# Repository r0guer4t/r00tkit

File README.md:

This handheld is meant to lower the barrier to hardware hacking.
Simple in its design and purpose. 
Superb at one thing because it neednt be bad at all things.

Technical specifications;
	Rockchip RK3328@1.5GHZ
	4 GB LPDDR3 
	32 GB microSD card
	ESP32s2
	5 in. LCD over HDMI
	2 USB 2.0 ports
	1 USB 3.0 port
	1 Ethernet jack

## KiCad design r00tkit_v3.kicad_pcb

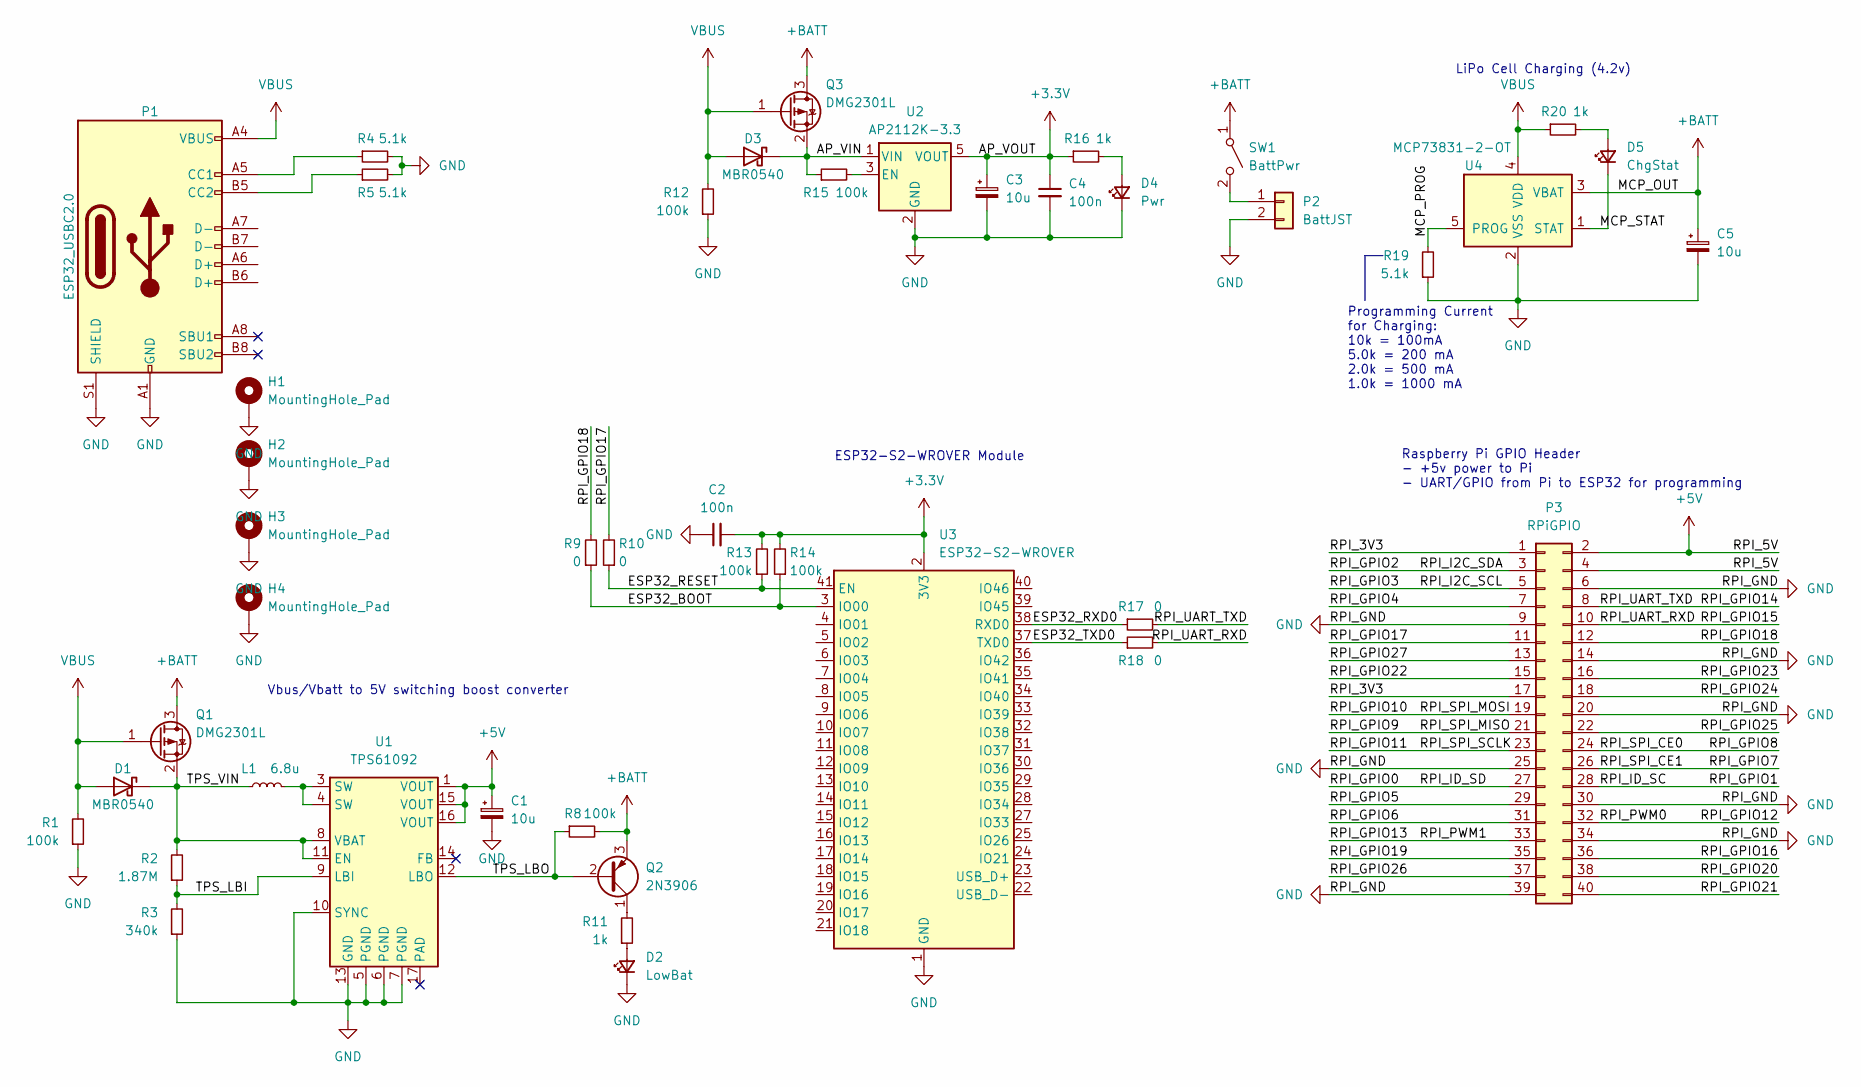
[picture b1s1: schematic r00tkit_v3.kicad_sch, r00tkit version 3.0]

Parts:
C1, C3, C5: 10u; C_1206_3216Metric_Pad1.33x1.80mm_HandSolder
C2, C4: 100n; C_1206_3216Metric_Pad1.33x1.80mm_HandSolder
D1, D3: MBR0540; D_SOD-123
D2: LowBat; D_1206_3216Metric_Pad1.42x1.75mm_HandSolder
D4: Pwr; D_1206_3216Metric_Pad1.42x1.75mm_HandSolder
D5: ChgStat; D_1206_3216Metric_Pad1.42x1.75mm_HandSolder
H1, H2, H3, H4: MountingHole_Pad; MountingHole_2.2mm_M2_DIN965_Pad
L1: 6.8u; L_2512_6332Metric_Pad1.52x3.35mm_HandSolder
P1: ESP32_USBC2.0; USB_C_Receptacle_Amphenol_12401548E4-2A
P2: BattJST; JST_GH_BM02B-GHS-TBT_1x02-1MP_P1.25mm_Vertical
P3: RPiGPIO; JST_PUD_B40B-PUDSS_2x20_P2.00mm_Vertical
Q1, Q3: DMG2301L; SOT-23
Q2: 2N3906; SOT-23
R1, R8, R12, R13, R14, R15: 100k; R_1206_3216Metric_Pad1.30x1.75mm_HandSolder
R2: 1.87M; R_1206_3216Metric_Pad1.30x1.75mm_HandSolder
R3: 340k; R_1206_3216Metric_Pad1.30x1.75mm_HandSolder
R4, R5, R19: 5.1k; R_1206_3216Metric_Pad1.30x1.75mm_HandSolder
R9, R10, R17, R18: 0; R_1206_3216Metric_Pad1.30x1.75mm_HandSolder
R11, R16, R20: 1k; R_1206_3216Metric_Pad1.30x1.75mm_HandSolder
SW1: BattPwr; SW_CuK_OS102011MA1QN1_SPDT_Angled
U1: TPS61092; Texas_S-PVQFN-N16_EP2.7x2.7mm_ThermalVias
U2: AP2112K-3.3; SOT-23-5
U3: ESP32-S2-WROVER
U4: MCP73831-2-OT; SOT-23-5

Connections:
+3.3V: C2.2, C3.1, C4.1, R13.2, R14.2, R16.1, U2.5 (VOUT), U3.2 (3V3)
+5V: C1.1, P3.2, P3.4, U1.1 (VOUT), U1.15 (VOUT), U1.16 (VOUT)
+BATT: C5.1, Q1.3 (D), Q2.3 (E), Q3.3 (D), R8.2, SW1.1 (A), U4.3 (VBAT)
/AP_VIN: D3.1 (K), Q3.2 (S), R15.1, U2.1 (VIN)
/ESP32_BOOT: R9.1, R14.1, U3.3 (IO00)
/ESP32_RESET: R10.1, R13.1, U3.41 (EN)
/ESP32_RXD0: R17.1, U3.38 (RXD0)
/ESP32_TXD0: R18.1, U3.37 (TXD0)
/MCP_PROG: R19.2, U4.5 (PROG)
/MCP_STAT: D5.1 (K), U4.1 (STAT)
/RPI_3V3: P3.1, P3.17
/RPI_GPIO0: P3.27
/RPI_GPIO1: P3.28
/RPI_GPIO2: P3.3
/RPI_GPIO3: P3.5
/RPI_GPIO4: P3.7
/RPI_GPIO5: P3.29
/RPI_GPIO6: P3.31
/RPI_GPIO7: P3.26
/RPI_GPIO8: P3.24
/RPI_GPIO9: P3.21
/RPI_GPIO10: P3.19
/RPI_GPIO11: P3.23
/RPI_GPIO12: P3.32
/RPI_GPIO13: P3.33
/RPI_GPIO14: P3.8, R17.2
/RPI_GPIO15: P3.10, R18.2
/RPI_GPIO16: P3.36
/RPI_GPIO17: P3.11, R10.2
/RPI_GPIO18: P3.12, R9.2
/RPI_GPIO19: P3.35
/RPI_GPIO20: P3.38
/RPI_GPIO21: P3.40
/RPI_GPIO22: P3.15
/RPI_GPIO23: P3.16
/RPI_GPIO24: P3.18
/RPI_GPIO25: P3.22
/RPI_GPIO26: P3.37
/RPI_GPIO27: P3.13
/TPS_LBI: R2.1, R3.2, U1.9 (LBI)
/TPS_LBO: Q2.2 (B), R8.1, U1.12 (LBO)
/TPS_VIN: D1.1 (K), L1.1, Q1.2 (S), R2.2, U1.8 (VBAT), U1.11 (EN)
GND: C1.2, C2.1, C3.2, C4.2, C5.2, D2.1 (K), D4.1 (K), H1.1, H2.1, H3.1, H4.1, P1.A1 (GND), P1.A12 (GND), P1.B1 (GND), P1.B12 (GND), P1.S1 (SHIELD), P2.2, P3.6, P3.14, P3.20, P3.25, P3.30, P3.34, P3.39, R1.1, R3.1, R4.2, R5.2, R12.1, R19.1, U1.5 (PGND), U1.6 (PGND), U1.7 (PGND), U1.10 (SYNC), U1.13 (GND), U2.2 (GND), U3.1 (GND), U3.26 (GND), U3.42 (GND), U3.43 (GND), U4.2 (VSS)
unnamed: D2.2 (A), R11.1
unnamed: D4.2 (A), R16.2
unnamed: D5.2 (A), R20.2
unnamed: L1.2, U1.3 (SW), U1.4 (SW)
unnamed: P1.A5 (CC1), R4.1
unnamed: P1.B5 (CC2), R5.1
unnamed: P2.1, SW1.2 (B)
unnamed: Q2.1 (C), R11.2
unnamed: R15.2, U2.3 (EN)
VBUS: D1.2 (A), D3.2 (A), P1.A4 (VBUS), P1.A9 (VBUS), P1.B4 (VBUS), P1.B9 (VBUS), Q1.1 (G), Q3.1 (G), R1.2, R12.2, R20.1, U4.4 (VDD)

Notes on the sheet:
ESP32-S2-WROVER Module
LiPo Cell Charging (4.2v)
Programming Current for Charging: 10k = 100mA 5.0k = 200 mA 2.0k = 500 mA 1.0k = 1000 mA
Raspberry Pi GPIO Header - +5v power to Pi - UART/GPIO from Pi to ESP32 for programming
Vbus/Vbatt to 5V switching boost converter

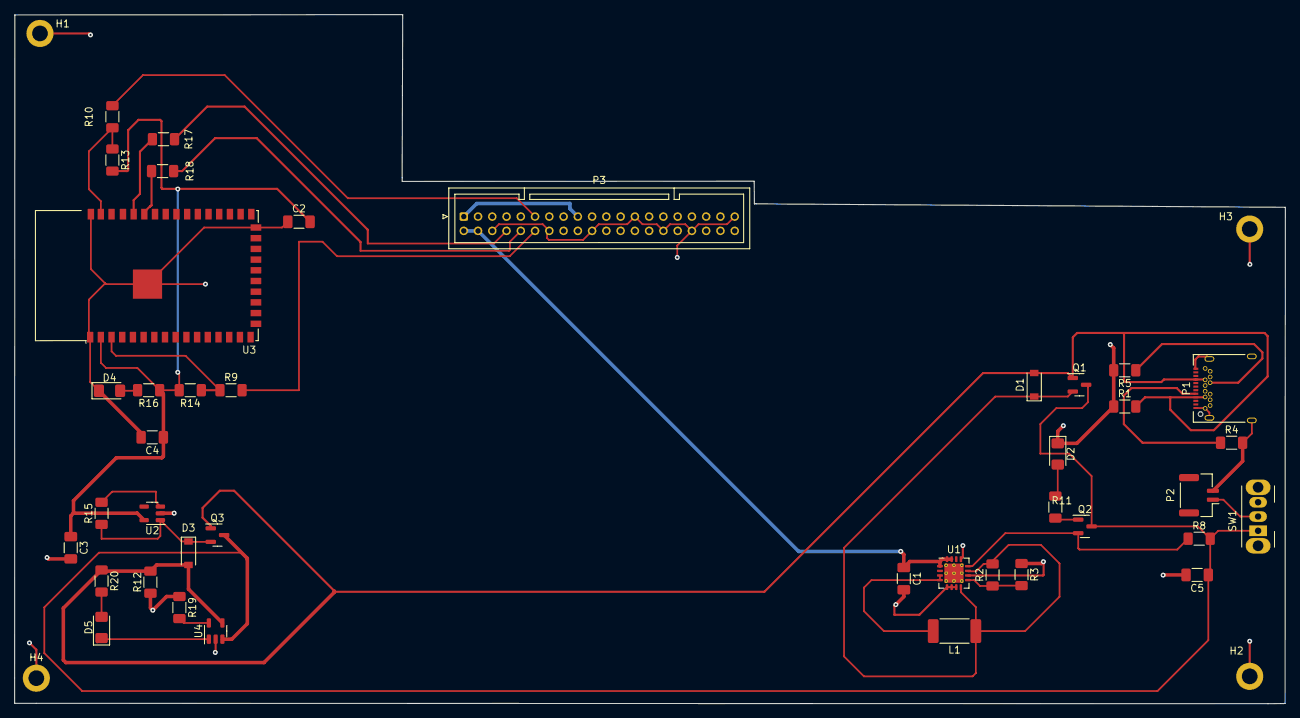
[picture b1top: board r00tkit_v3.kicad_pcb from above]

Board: 4 copper layers, 178.2 x 96.6 mm, 44 parts (0 on the bottom side), 29 nets.

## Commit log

2023-03-05 schematics and netlist
2023-03-06 .pro files
2023-04-04 r00tkit_v3 sample project in KiCad 6
    Modeled off of the Adafruit Feather ESP32-S2 development board. All LiPo cells in parallel for 3.7v, boosting to 5V for the Pi.
2023-05-05 modified schematic and routed PCB
